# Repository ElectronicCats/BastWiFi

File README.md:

# BastWiFi

## License

Electronic Cats invests time and resources providing this open source design, please support Electronic Cats and open-source hardware by purchasing products from Electronic Cats!

Designed by Electronic Cats.

Firmware released under an GNU AGPL v3.0 license. See the LICENSE file for more information.

Hardware released under an CERN Open Hardware Licence v1.2. See the LICENSE_HARDWARE file for more information.

Electronic Cats is a registered trademark, please do not use if you sell these PCBs.

Jun 2020

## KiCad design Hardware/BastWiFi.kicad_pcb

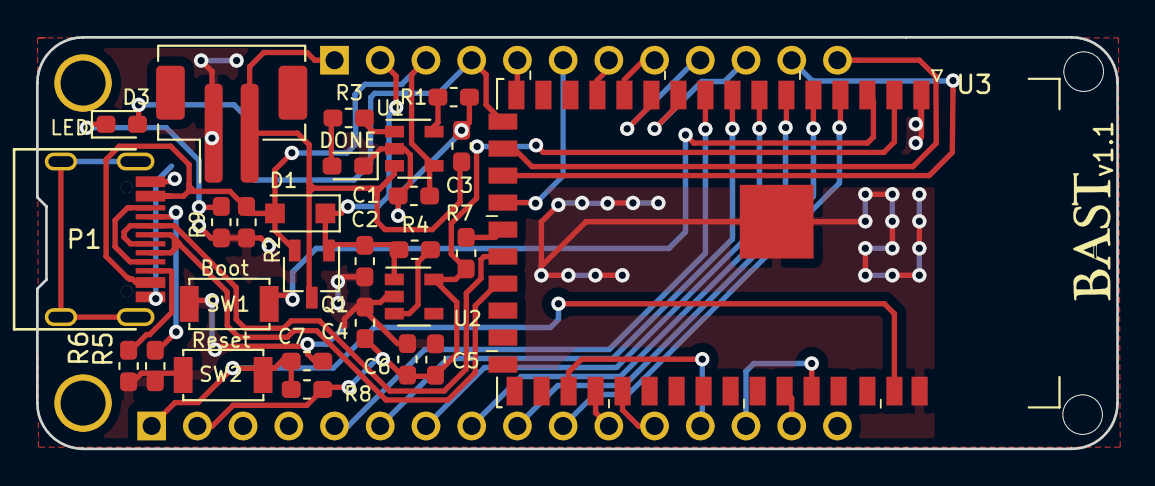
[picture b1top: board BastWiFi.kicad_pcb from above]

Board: 2 copper layers, 60.0 x 22.9 mm, 29 parts (0 on the bottom side), 37 nets.

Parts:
C1, C2, C3, C4, C5: 10uF; C_0603_1608Metric_Pad1.05x0.95mm_HandSolder
C6: 0.1uF; C_0603_1608Metric_Pad1.05x0.95mm_HandSolder
C7: 1uF; C_0603_1608Metric_Pad1.05x0.95mm_HandSolder
D1: MBR120; D_SOD-123F
D2: DONE; D_0603_1608Metric_Pad1.05x0.95mm_HandSolder
D3: LED; LED_0603_1608Metric_Pad1.05x0.95mm_HandSolder
J1: Conn_Battery; JST_PH_B2B-PH-SM4-TB_1x02-1MP_P2.00mm_Vertical
J3: Conn_Left; PinSocket_1x16_P2.54mm_Vertical
J4: Conn_Right; PinSocket_1x12_P2.54mm_Vertical
P1: USB_C_Plug_USB2.0; C393939
Q1: DMG3415U-7; TSOT-23
R1: 2K; R_0603_1608Metric_Pad1.05x0.95mm_HandSolder
R2: 100K; R_0603_1608Metric_Pad1.05x0.95mm_HandSolder
R3, R9: 1K; R_0603_1608Metric_Pad1.05x0.95mm_HandSolder
R4, R7, R8: 10K; R_0603_1608Metric_Pad1.05x0.95mm_HandSolder
R5, R6: 5.1K; R_0603_1608Metric_Pad1.05x0.95mm_HandSolder
SW1: GPIO0; C455281
SW2: RESET; C455281
U1: MCP73831-3-OT; SOT-23-5
U2: AP2112K-3.3; SOT-23-5
U3: ESP32-S2-WROVER

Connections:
+3V3: C4.1, C5.1, C6.1, J3.2, R7.1, R8.1, U2.5, U3.2
+BATT: C3.1, J1.2, J4.1, Q1.3, U1.3
/A0: J3.10, U3.4
/A1: J3.9, U3.5
/A2: J3.8, U3.6
/A3: J3.7, U3.7
/A4: J3.6, U3.8
/A5: J3.5, U3.9
/D+: P1.A6, U3.23
/D-: P1.A7, U3.22
/EN: C2.1, D1.1, J4.2, Q1.1, R4.2, U2.1
/GPIO0: SW1.2, U3.3
/GPIO05: J4.10, U3.10
/GPIO06: J4.9, U3.11
/GPIO09: J4.8, U3.12
/GPIO10: J4.7, U3.13
/GPIO11: J4.6, U3.20
/GPIO12: J4.5, U3.16
/GPIO13: D3.2, J4.4, U3.17
/GPIO18: R7.2, U3.21
/MISO: J3.13, U3.29
/MOSI: J3.12, U3.31
/RX: J3.14, U3.38
/SCK: J3.11, U3.30
/SCL: J4.11, U3.19
/SDA: J4.12, U3.18
/TX: J3.15, U3.37
/~RST~: C7.1, J3.1, R8.2, SW2.2, U3.41
GND: C1.2, C2.2, C3.2, C4.2, C5.2, C6.2, C7.2, D2.1, J1.1, J3.4, P1.A1, R1.2, R2.2, R5.1, R6.1, R9.2, SW1.1, SW2.1, U1.2, U2.2, U3.1, U3.26, U3.42, U3.43
unnamed: D2.2, R3.2
unnamed: D3.1, R9.1
unnamed: P1.A5, R5.2
unnamed: P1.B5, R6.2
unnamed: R1.1, U1.5
unnamed: R3.1, U1.1
unnamed: R4.1, U2.3
VBUS: C1.1, D1.2, J4.3, P1.A4, Q1.2, R2.1, U1.4

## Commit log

2020-04-25 init schematic and PCB
2020-06-02 Change footprint sw
2020-06-05 Tracks
2020-06-05 Add connector
2020-06-09 Route
2020-06-10 Change tracks
2020-06-10 Add change sch
2020-06-11 Add button
2020-06-11 Change button
2020-06-11 Change sch
2020-06-13 Change footprint
2020-06-15 update schematic
2020-06-16 add LED
2020-06-16 BOM added
2020-06-16 xml update
2020-06-30 Change Rev
2020-07-03 Last Revision
2020-07-09 Change pin
2020-08-06 change pads
2020-09-03 Update README.md
    Added licenses
2020-09-23 3D Model
2020-09-25 Change_name_pin
2021-01-14 datasheet
2021-01-14 rename datasheet
2021-01-20 Create LICENSE_HARDWARE
